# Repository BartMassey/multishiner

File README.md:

# MultiShiner
Copyright &copy; 2015 Bart and Benjamin Massey

This KiCAD project is a tiny circuit board with a Silicon
Labs EFM8BB10 microcontroller and not much else. The board
is intended to be put into the arm of a GameCube controller,
where it intercepts the data flowing between the controller
and the cube. With the proper software, the board can be
made to "multi-shine" the Smash Brothers Melee character
"Fox" when a newly-added pushbutton switch on the side of
the controller is pressed.

The project is in the early stages. The hardware is not
finished; the software is nonexistent.

Working with this project requires a recent (post-stable)
version of KiCAD.

## License

The hardware design and source code for this project is
available under the MIT License. See the file COPYING in
this distribution for license terms.

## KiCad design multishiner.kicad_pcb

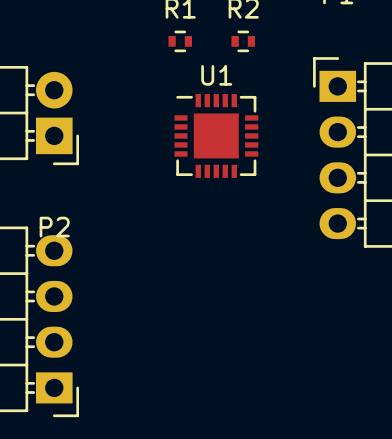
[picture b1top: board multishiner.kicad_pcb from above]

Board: 2 copper layers, 6 parts (0 on the bottom side), 7 nets, no tracks yet.

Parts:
P1: DEBUG; Pin_Header_Angled_1x04
P2: SWITCH; Pin_Header_Angled_1x02
P3: CTLR; Pin_Header_Angled_1x04
R1, R2: 1K; R_0402
U1: EFM8BB10; QFN-20-1EP_4x4mm_Pitch0.5mm

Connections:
/CTLR_D: P3.2, R1.2, U1.20
/CUBE_D: P3.3, R2.2, U1.19
GND: P1.1, P2.1, P3.4, U1.3
unnamed: P1.3, U1.5
unnamed: P1.4, U1.6
unnamed: P2.2, U1.1
VDD: P1.2, P3.1, R1.1, R2.1, U1.4

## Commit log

2015-08-20 multishiner board in KiCAD
